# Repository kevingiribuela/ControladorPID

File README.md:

# ControladorPID
 Controlador PID desarrollado en 4to año de la carrera

## Descripción
Este diseño se realizó basandose en los principios del control robusto. El objetivo es realizar el control automático de una planta conocida pero cuyos parámetros pueden variar en función de agentes externos como lo son la temperatura, la humedad, etc. Es por eso que el controlador debe no solo controlar a la planta nominal sino que también a la familia de plantas involucradas en el modelo. 

La planta se trata de una serie de filtros pasabajos en cascada implementados con amplificadores operacionales, resistencias y capacitores. Los archivos correspondientes al diseño de la placa se encuentran en la presente documentación.

La placa es capaz de realizar una identificación de la planta a partir de un escalón a su entrada y enviar los datos en tiempo real a MATLAB para su procesamiento de datos y posterior modelado a partir de un modelo de primer orden.

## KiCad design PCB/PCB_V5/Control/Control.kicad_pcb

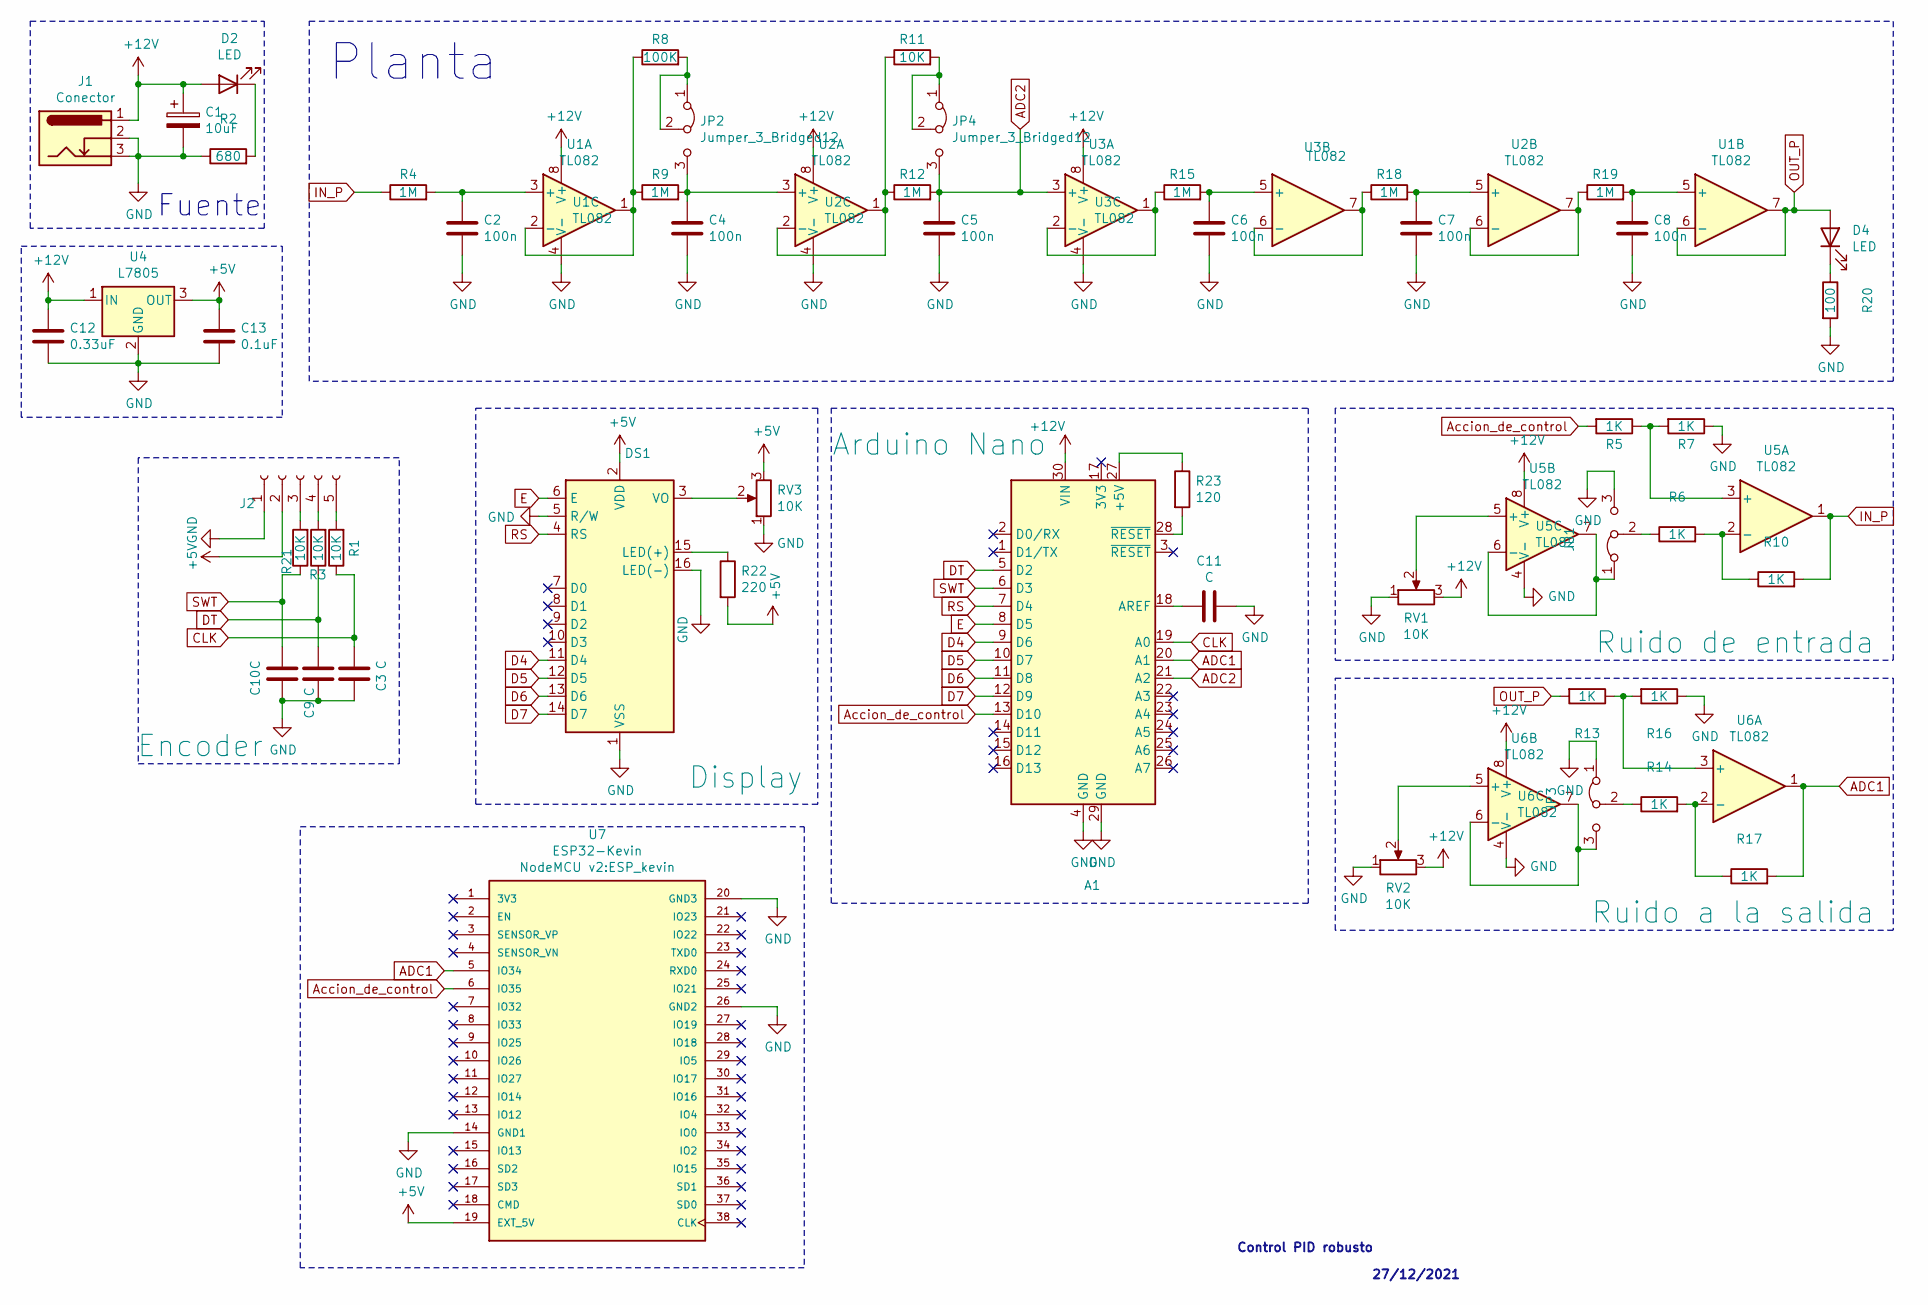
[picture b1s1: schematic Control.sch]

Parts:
A1: Arduino Nano; Arduino_Nano_WithMountingHoles
C1: 10uF; CP_Radial_D4.0mm_P1.50mm
C2, C4, C5, C6, C7, C8: 100n; C_Disc_D4.3mm_W1.9mm_P5.00mm
C3, C9, C10, C11: C; C_Disc_D4.3mm_W1.9mm_P5.00mm
C12: 0.33uF; C_Disc_D4.3mm_W1.9mm_P5.00mm
C13: 0.1uF; C_Disc_D4.3mm_W1.9mm_P5.00mm
D2, D4: LED; LED_D5.0mm_Clear
DS1: Display; WC1602A
J1: Conector; BarrelJack_Wuerth_6941xx301002
J2: Encoder; PinHeader_1x05_P2.54mm_Vertical
JP1: Ruido de entrada; PinHeader_1x03_P2.54mm_Vertical
JP2, JP4: Jumper_3_Bridged12; PinHeader_1x03_P2.54mm_Vertical
JP3: Ruido a la salida; PinHeader_1x03_P2.54mm_Vertical
R1, R11: 10K; R_Axial_DIN0204_L3.6mm_D1.6mm_P7.62mm_Horizontal
R2: 680; R_Axial_DIN0204_L3.6mm_D1.6mm_P7.62mm_Horizontal
R3, R21: 10K; R_Axial_DIN0309_L9.0mm_D3.2mm_P25.40mm_Horizontal
R4, R9, R12, R15, R18, R19: 1M; R_Axial_DIN0204_L3.6mm_D1.6mm_P7.62mm_Horizontal
R5, R6, R7, R10, R13, R14, R16, R17: 1K; R_Axial_DIN0204_L3.6mm_D1.6mm_P7.62mm_Horizontal
R8: 100K; R_Axial_DIN0204_L3.6mm_D1.6mm_P7.62mm_Horizontal
R20: 100; R_Axial_DIN0204_L3.6mm_D1.6mm_P7.62mm_Horizontal
R22: 220; R_Axial_DIN0204_L3.6mm_D1.6mm_P7.62mm_Horizontal
R23: 120; R_Axial_DIN0204_L3.6mm_D1.6mm_P7.62mm_Horizontal
RV1, RV2, RV3: 10K; Potentiometer_Bourns_3266Y_Vertical
U1, U2, U3: TL082; DIP-8_W7.62mm_Socket
U4: L7805; TO-220-3_Vertical
U5, U6: TL082; DIP-8_W7.62mm
U7: ESP32-Kevin; ESP_kevin; PARTREV 4

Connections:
+5V: C13.1, DS1.2 (VDD), J2.2, R22.2, RV3.3, U4.3 (OUT), U7.19 (EXT_5V)
+12V: A1.30 (VIN), C1.1, C12.1, D2.2 (A), J1.1, RV1.3, RV2.3, U1.8 (V+), U2.8 (V+), U3.8 (V+), U4.1 (IN), U5.8 (V+), U6.8 (V+)
ADC1: A1.20 (A1), R17.2, U6.1, U7.5 (IO34)
ADC2: A1.21 (A2), C5.1, JP4.3 (B), R12.2, U3.3 (+)
Accion_de_control: A1.13 (D10), R5.2, U7.6 (IO35)
CLK: A1.19 (A0), C3.2, R1.1
D4: A1.9 (D6), DS1.11 (D4)
D5: A1.10 (D7), DS1.12 (D5)
D6: A1.11 (D8), DS1.13 (D6)
D7: A1.12 (D9), DS1.14 (D7)
DT: A1.5 (D2), C9.1, R3.1
E: A1.8 (D5), DS1.6 (E)
GND: A1.4 (GND), A1.29 (GND), C1.2, C2.2, C3.1, C4.2, C5.2, C6.2, C7.2, C8.2, C9.2, C10.2, C11.1, C12.2, C13.2, DS1.1 (VSS), DS1.5 (R/W), DS1.16 (LED(-)), J1.2, J1.3, J2.1, JP1.3 (B), JP3.1 (A), R2.1, R7.1, R16.1, R20.2, RV1.1, RV2.1, RV3.1, U1.4 (V-), U2.4 (V-), U3.4 (V-), U4.2 (GND), U5.4 (V-), U6.4 (V-), U7.14 (GND1), U7.20 (GND3), U7.26 (GND2)
IN_P: R4.1, R10.2, U5.1
unnamed: A1.18 (AREF), C11.2
unnamed: A1.27 (+5V), R23.1
unnamed: A1.28 (~RESET), R23.2
unnamed: C2.1, R4.2, U1.3 (+)
unnamed: C4.1, JP2.3 (B), R9.2, U2.3 (+)
unnamed: C6.1, R15.2, U3.5 (+)
unnamed: C7.1, R18.2, U2.5 (+)
unnamed: C8.1, R19.2, U1.5 (+)
unnamed: D2.1 (K), R2.2
unnamed: D4.1 (K), R20.1
unnamed: DS1.3 (VO), RV3.2
unnamed: DS1.15 (LED(+)), R22.1
unnamed: J2.3, R21.2
unnamed: J2.4, R3.2
unnamed: J2.5, R1.2
unnamed: JP1.1 (A), U5.6 (-), U5.7
unnamed: JP1.2 (C), R6.1
unnamed: JP2.1 (A), JP2.2 (C), R8.2
unnamed: JP3.2 (C), R14.1
unnamed: JP3.3 (B), U6.6 (-), U6.7
unnamed: JP4.1 (A), JP4.2 (C), R11.2
unnamed: R5.1, R7.2, U5.3 (+)
unnamed: R8.1, R9.1, U1.1, U1.2 (-)
unnamed: R6.2, R10.1, U5.2 (-)
unnamed: R11.1, R12.1, U2.1, U2.2 (-)
unnamed: R13.1, R16.2, U6.3 (+)
unnamed: R14.2, R17.1, U6.2 (-)
unnamed: R15.1, U3.1, U3.2 (-)
unnamed: R18.1, U3.6 (-), U3.7
unnamed: R19.1, U2.6 (-), U2.7
unnamed: RV1.2, U5.5 (+)
unnamed: RV2.2, U6.5 (+)
OUT_P: D4.2 (A), R13.2, U1.6 (-), U1.7
RS: A1.7 (D4), DS1.4 (RS)
SWT: A1.6 (D3), C10.1, R21.1

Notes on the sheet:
27/12/2021
Control PID robusto
Planta
Fuente

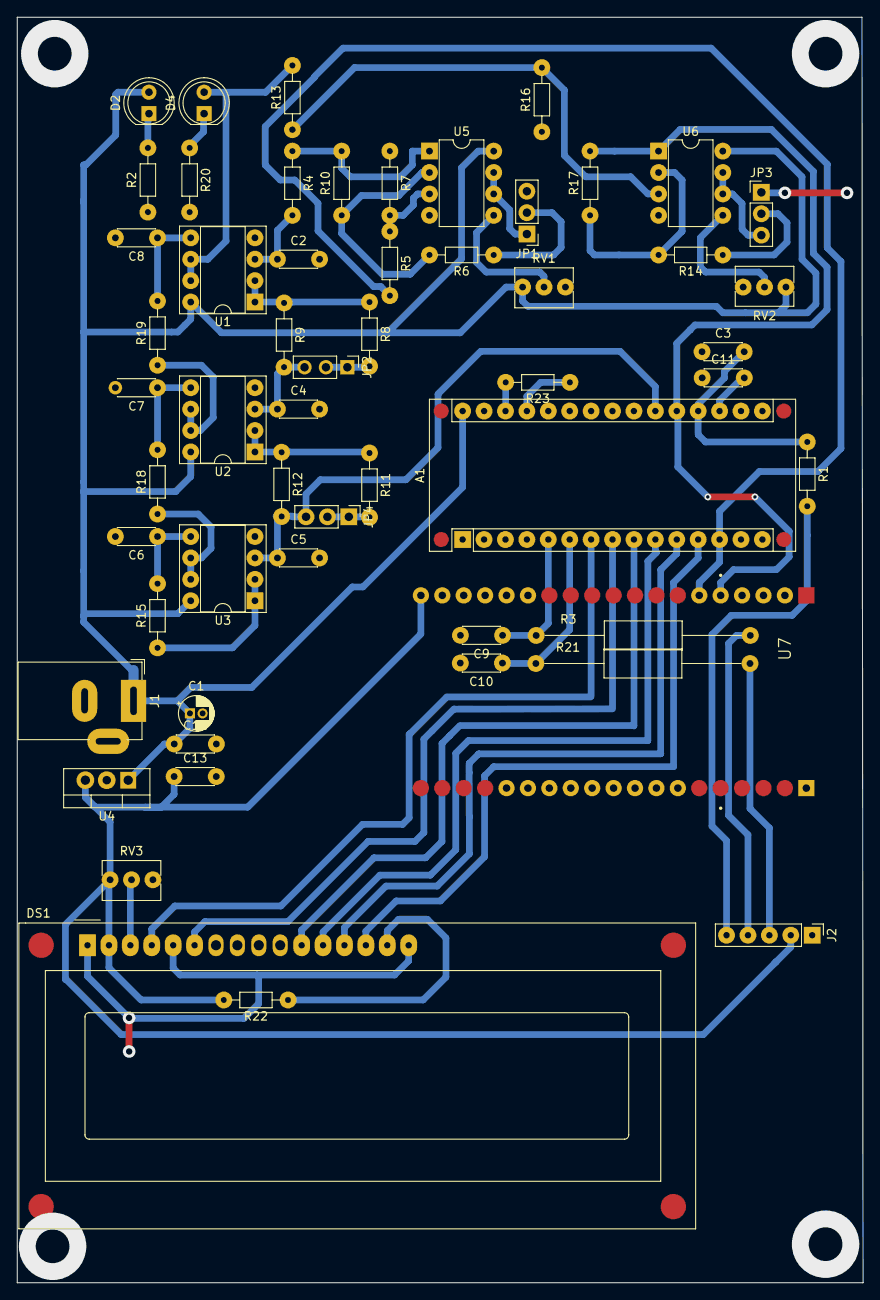
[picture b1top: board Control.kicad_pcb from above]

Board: 2 copper layers, 100.3 x 150.1 mm, 56 parts (0 on the bottom side), 49 nets.

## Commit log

2023-01-11 Commit inicial
2023-01-11 Commit de imagenes
